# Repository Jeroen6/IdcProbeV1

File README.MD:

# IdcProbeV1
Invasive isolated DC Current probe based on Sensitec CMS3000

## What

This USB 5V powered current sensor should provide an relatively cheap way to safely scope AC or DC current.  
It should provide isolation up to 4 kV (rms), meaning it can measure anywhere in a circuit.

The high bandwidth and accuracy of the Sensitec module made it almost like a normal shunt.

Transfer ratio of the 5A and 15A unit would be 1A:1V and 1A:0.1V respectively.

## Challenges
The challenges involved in this project are powering the Sensitec sensor from a USB port, commonly found on most modern scopes.  
This required a high frequency (1.3 Mhz) DC-DC converter to create positive ands negative 12V for the sensor.  
Several prototypes have shown this is not an easy job, keeping ripple low is difficult with >1 MHz converters.

Due to the capacitance required for the DC-DC converter a high inrush current needs to be reduced on the USB input.

## Progress so far
So far two working prototypes have been made (photo) and used thoroughly this year, it was extremely useful!  
Several important changes to the circuit have been made, both to the DC-DC, the input current, and oscillation prevention on the output with long BNC cables.

*(high-res in media folder)*

However, when (winter)time came to continue this project sad news arrived.  
[Sensitec discontinued the CMS and CDS current sensor families][1], with the [CFS1000][2] chip as alternative.

## Future
The CFS1000 is a more versatile product. Which is an advantage, but not if you required on the engineering and factory calibration of the CMS3000.
The CFS series requires development of an external sensing busbar and calibration procedure, both exceed my initial intended complexity of this project. But I might change my mind.

I will probably not persue development of this project, apart from assembling a few units for peronal use.  

*If someone has ideas to revive this project, let me know (make an issue or something)*

[1]: https://github.com/Jeroen6/IdcProbeV1/blob/master/doc/Sensitec%20-%20CMS3000%20-%20Current%20sensor%20discontinuation%20notice.pdf
[2]: https://github.com/Jeroen6/IdcProbeV1/blob/master/doc/Sensited%20-%20CFS1000%20-%20%20Integrated%20MagnetoResistive%20Current%20Sensor.pdf

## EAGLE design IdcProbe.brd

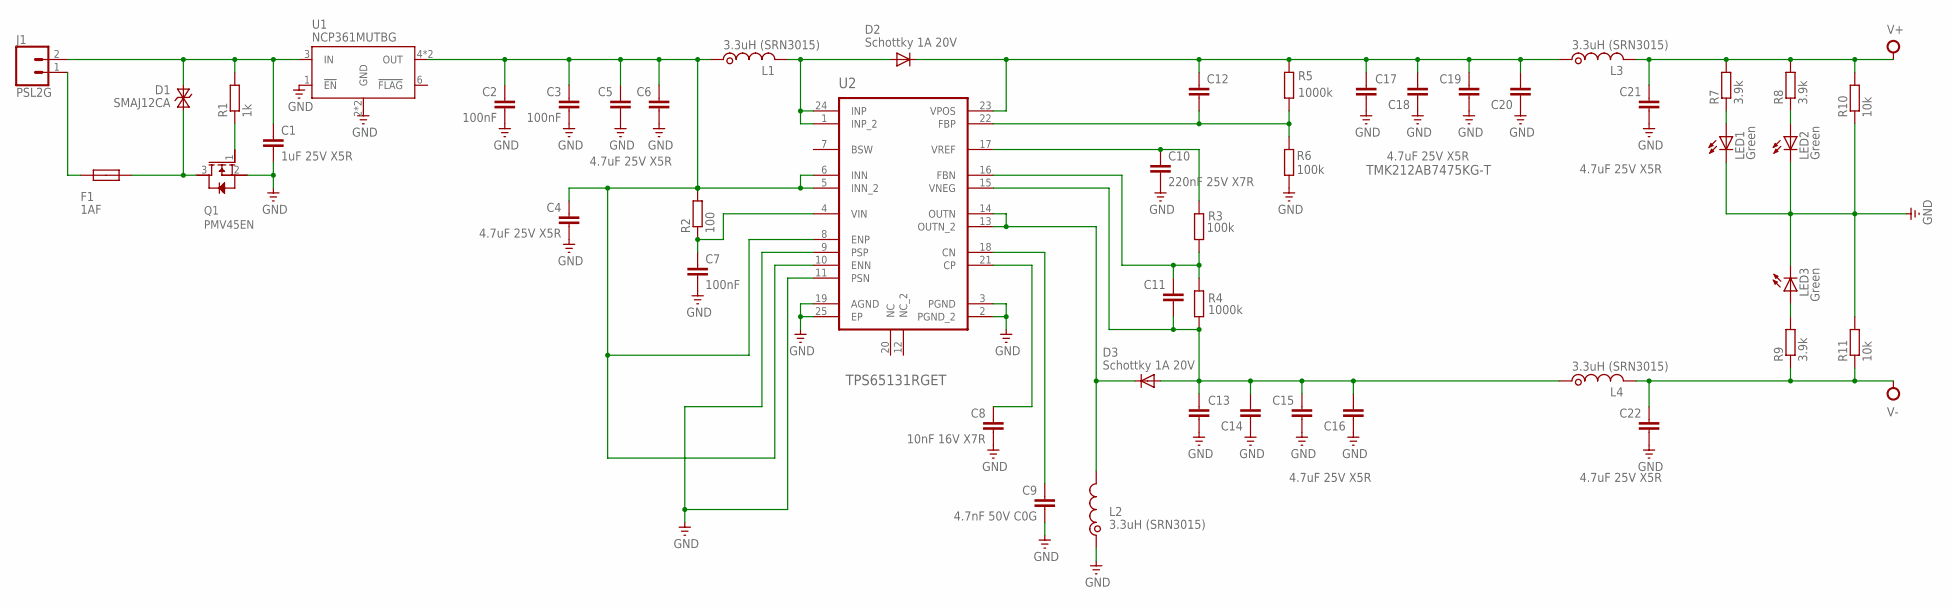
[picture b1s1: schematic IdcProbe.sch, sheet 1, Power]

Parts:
C1: 1uF 25V X5R; C0805; MPN TMK212AB7475KG-T
C2, C3, C7: 100nF; C0805
C4, C5, C6, C13, C14, C15, C16, C17, C18, C19, C20, C21, C22: 4.7uF 25V X5R; C0805; MPN TMK212AB7475KG-T
C8: 10nF 16V X7R; C0805
C9: 4.7nF 50V C0G; C0805
C10: 220nF 25V X7R; C0805
C11, C12: C-EUC0805; C0805
D1: SMAJ12CA; SMA_NOPOL
D2, D3: Schottky 1A 20V; SOD323-R; MPN PMEG4010BEA
F1: 1AF; 1206_HV
J1: PSL2G; MOLEX-1X2
L1, L2, L3, L4: 3.3uH (SRN3015); VLS3015
LED1: Green; LED3MM
LED2, LED3: Green; CHIP-LED0805
Q1: PMV45EN; SOT23
R1: 1k; R0805I
R2: 100; R0805I
R3, R6: 100k; R0805I
R4, R5: 1000k; R0805I
R7, R8, R9: 3.9k; R0805I
R10, R11: 10k; R0805I
U1: NCP361MUTBG; UDFN6_2X2; MPN TMK212AB7475KG-T
U2: TPS65131RGET; QFN50P400X400X100-25N

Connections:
CN: C9.1, U2.18 (CN)
CP: C8.1, U2.21 (CP)
FBN: C11.1, R3.1, R4.1, U2.16 (FBN)
FBP: C12.2, R5.1, R6.2, U2.22 (FBP)
GND: C1.2, C2.2, C3.2, C4.2, C5.2, C6.2, C7.2, C8.2, C9.2, C10.2, C13.2, C14.2, C15.2, C16.2, C17.2, C18.2, C19.2, C20.2, C21.2, C22.2, L2.1, LED1.K (C), LED2.C, LED3.C, Q1.2 (S), R6.1, R10.1, R11.2, U1.1 (!EN), U1.2 (GND), U1.7 (GND), U2.2 (PGND_2), U2.3 (PGND), U2.9 (PSP), U2.11 (PSN), U2.19 (AGND), U2.25 (EP); also elsewhere on the board
INP: D2.A, L1.2, U2.1 (INP_2), U2.24 (INP)
unnamed: LED2.A, R8.1
unnamed: LED3.A, R9.2
unnamed: LED1.A, R7.1
unnamed: C1.1, D1.2 (C), J1.2, R1.2, U1.3 (IN)
unnamed: D1.1 (A), F1.P$1, Q1.3 (D)
unnamed: Q1.1 (G), R1.1
unnamed: F1.P$2, J1.1
OUTN: D3.C, L2.2, U2.13 (OUTN_2), U2.14 (OUTN)
RV+: C12.1, C17.1, C18.1, C19.1, C20.1, D2.C, L3.1, R5.2, U2.23 (VPOS)
RV-: C11.2, C13.1, C14.1, C15.1, C16.1, D3.A, L4.1, R4.2, U2.15 (VNEG)
V+: C21.1, L3.2, R7.2, R8.2, R10.2; also elsewhere on the board
V-: C22.1, L4.2, R9.1, R11.1; also elsewhere on the board
VI: C2.1, C3.1, C4.1, C5.1, C6.1, L1.1, R2.2, U1.4 (OUT), U1.5 (OUT), U2.5 (INN_2), U2.6 (INN), U2.8 (ENP), U2.10 (ENN)
VIN: C7.1, R2.1, U2.4 (VIN)
VREF: C10.1, R3.2, U2.17 (VREF)

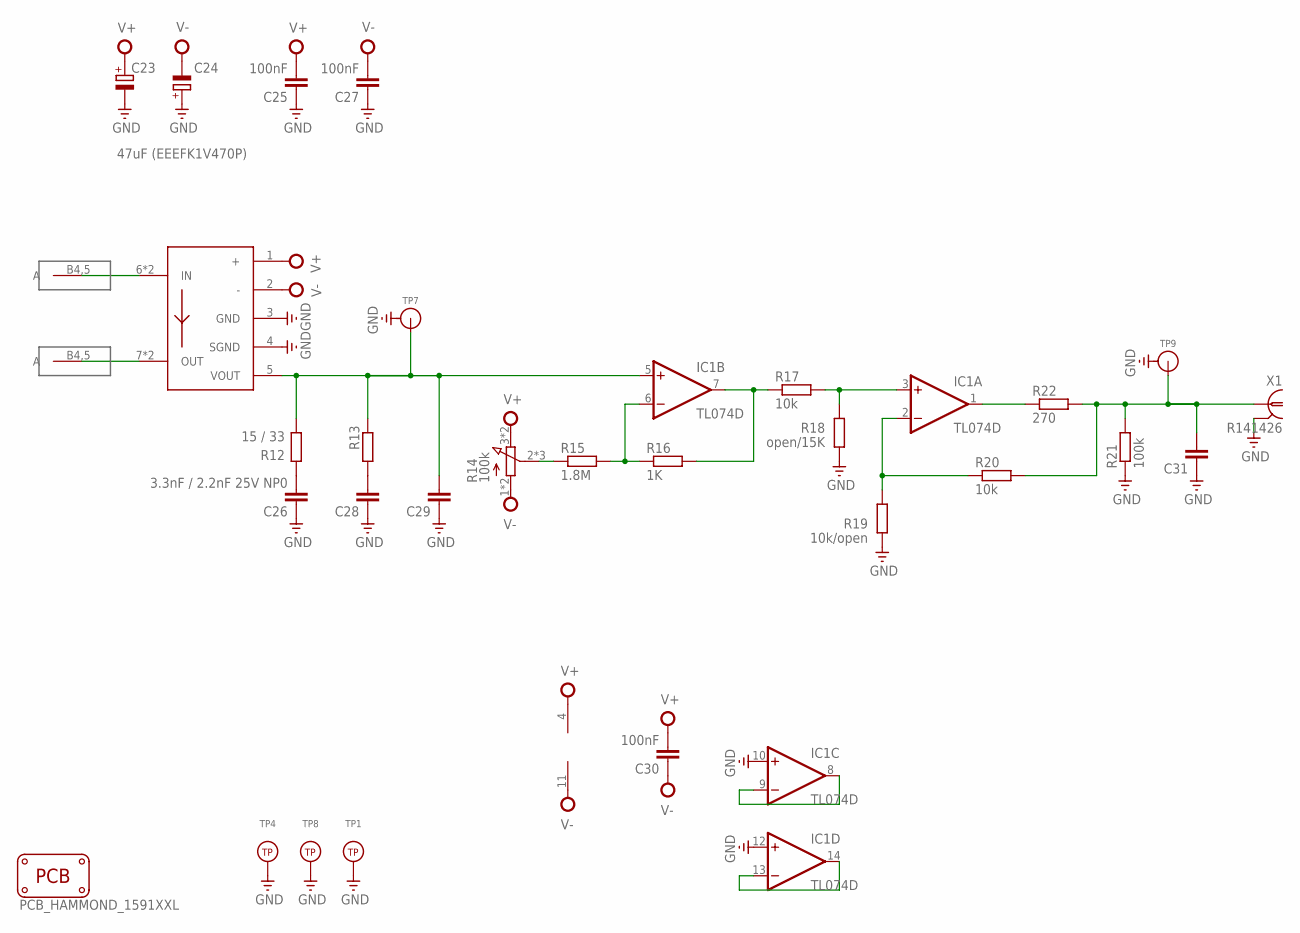
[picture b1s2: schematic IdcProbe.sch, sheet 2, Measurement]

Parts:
C23, C24: 47uF (EEEFK1V470P); PANASONIC_D
C25, C27, C30: 100nF; C0805
C26: 3.3nF / 2.2nF 25V NP0; C0805
C28, C29, C31: C-EUC0805; C0805
H1: PCB_HAMMOND_1591XXL; HMD_MFG_1591XXL
IC1: TL074D; SO14
P1, P2: BANANA_SOCKETVERTICAL; 4,5-PAD
R12: 15 / 33; R0805
R13: R-EU_R0805; R0805
R14: 100k; 3386-MULTI; MPN 3386P-1-104LF
R15: 1.8M; R0805
R16: 1K; R0805
R17, R20: 10k; R0805I
R18: open/15K; R0805I
R19: 10k/open; R0805I
R21: 100k; R0805
R22: 270; R0805
TP1, TP4, TP8: TESTPOINT; TESTHOOK
TP7, TP9: TESTPOINT_GND; PROBE_POINT
U3: CMS3005; CMS3015
X1: R141426

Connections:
GND: C23.-, C24.+, C25.1, C26.1, C27.1, C28.1, C29.1, C31.1, IC1.10 (+IN), IC1.12 (+IN), R18.1, R19.1, R21.1, TP1.TP, TP4.TP, TP7.GND, TP8.TP, TP9.GND, U3.3 (GND), U3.4 (SGND), X1.2, X1.3 (2), X1.4 (2), X1.5 (2); also elsewhere on the board
unnamed: IC1.7 (OUT), R16.2, R17.1
unnamed: IC1.6 (-IN), R15.2, R16.1
unnamed: P1.B4,5, U3.6 (IN), U3.6' (IN)
unnamed: P2.B4,5, U3.7 (OUT), U3.7' (OUT)
unnamed: IC1.8 (OUT), IC1.9 (-IN)
unnamed: IC1.13 (-IN), IC1.14 (OUT)
unnamed: C26.2, R12.2
unnamed: C28.2, R13.2
unnamed: C31.2, R20.2, R21.2, R22.2, TP9.TP, X1.1
unnamed: C29.2, IC1.5 (+IN), R12.1, R13.1, TP7.TP, U3.5 (VOUT)
unnamed: IC1.2 (-IN), R19.2, R20.1
unnamed: R14.2 (SW), R14.5 (SW), R14.7 (SW), R15.1
unnamed: IC1.3 (+IN), R17.2, R18.2
unnamed: IC1.1 (OUT), R22.1
V+: C23.+, C25.2, C30.2, IC1.4 (V+), R14.3 (CW), R14.6 (CW), U3.1 (+); also elsewhere on the board
V-: C24.-, C27.2, C30.1, IC1.11 (V-), R14.1 (CCW), R14.4 (CCW), U3.2 (-); also elsewhere on the board

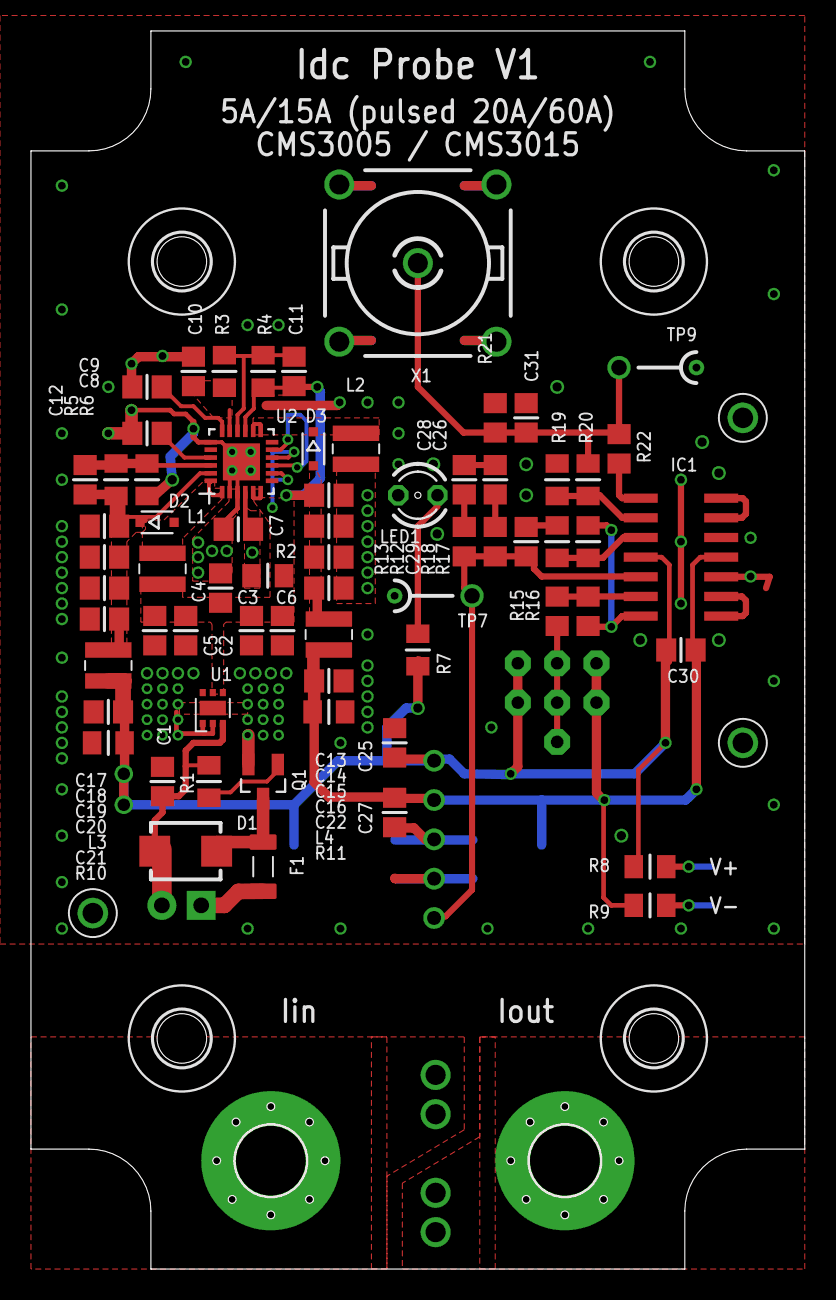
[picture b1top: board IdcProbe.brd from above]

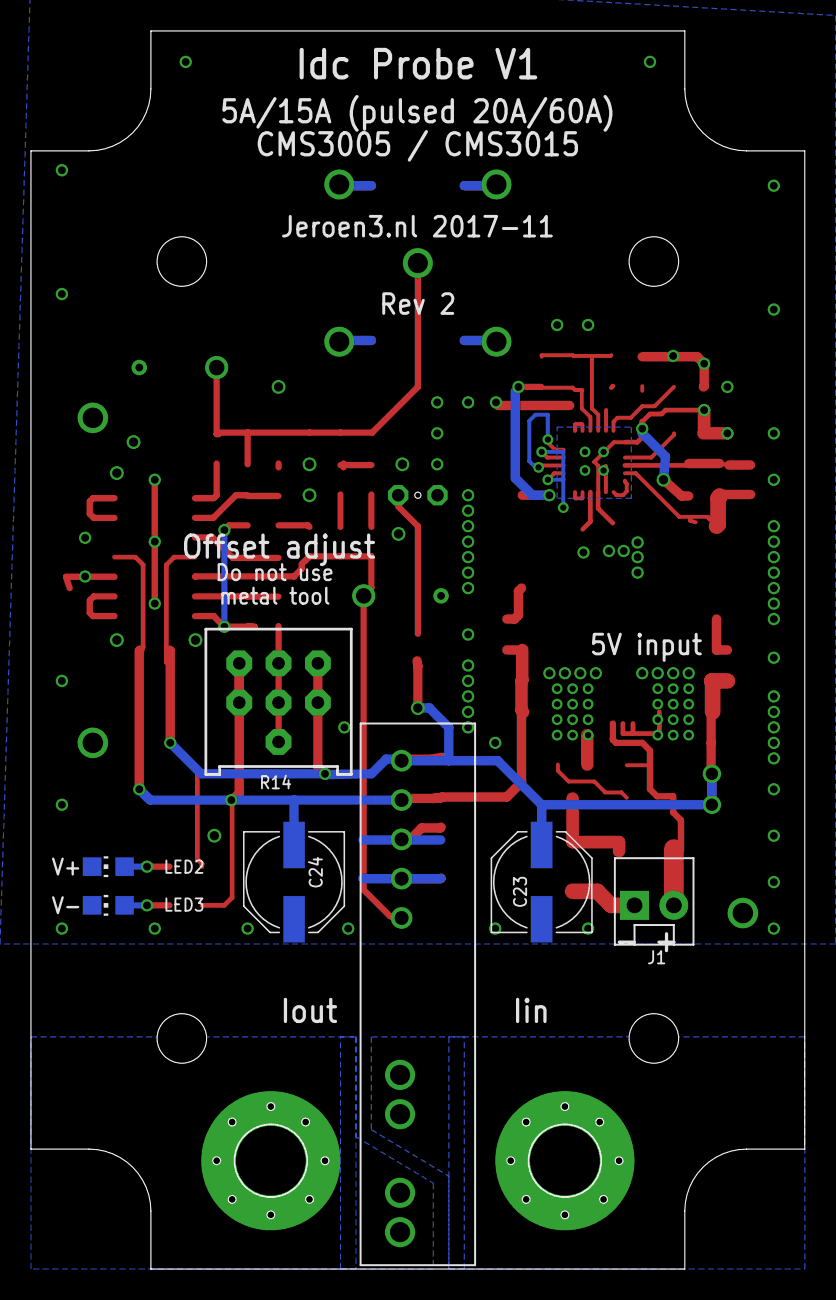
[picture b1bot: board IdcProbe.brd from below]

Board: 2 copper layers, 49.9 x 79.9 mm, 79 parts (7 on the bottom side), 35 nets.

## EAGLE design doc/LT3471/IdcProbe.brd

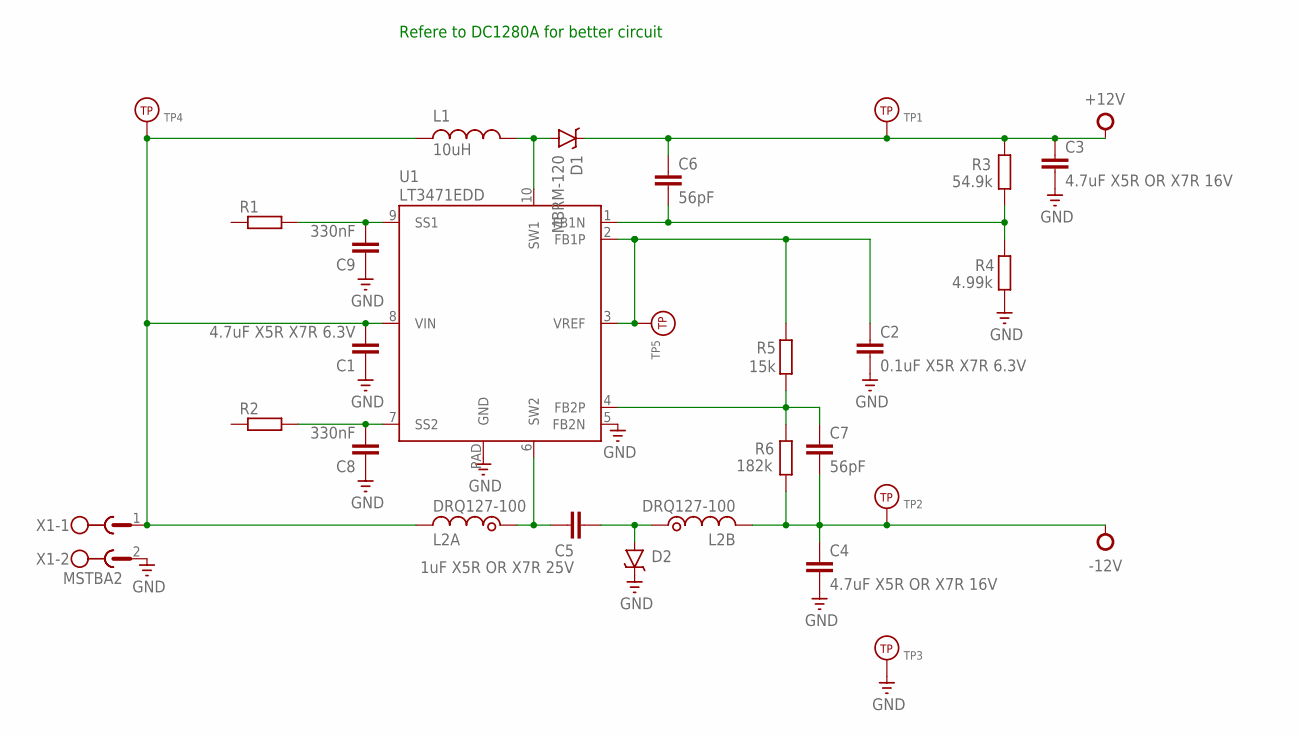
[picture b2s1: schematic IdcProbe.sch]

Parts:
C1: 4.7uF X5R X7R 6.3V; C0603
C2: 0.1uF X5R X7R 6.3V; C0603
C3, C4: 4.7uF X5R OR X7R 16V; C0603
C5: 1uF X5R OR X7R 25V; C0603
C6, C7: 56pF; C0603
C8, C9: 330nF; C0603
D1, D2: MBRM-120; POWERMITE1
L1: 10uH; 242408FPS; MPN 242408FPS‑220M‑01
L2: DRQ127-100; DRQ127
R1, R2: R-EU_R0603; R0603
R3: 54.9k; R0603
R4: 4.99k; R0603
R5: 15k; R0603
R6: 182k; R0603
TP1, TP2, TP3, TP4, TP5: TESTPOINT; TESTHOOK
U1: LT3471EDD; DFN10-3X3
X1: MSTBA2

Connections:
+12V: C3.1, C6.1, D1.1 (C), R3.2, TP1.TP
-12V: C4.1, C7.2, L2.4 (2), R6.1, TP2.TP
GND: C1.1, C2.2, C3.2, C4.2, C8.1, C9.1, D2.1 (C), R4.1, TP3.TP, U1.5 (FB2N), U1.PAD (GND), X1.2
unnamed: C9.2, R1.2, U1.9 (SS1)
unnamed: C8.2, R2.2, U1.7 (SS2)
unnamed: C1.2, L1.1, L2.3 (2), TP4.TP, U1.8 (VIN), X1.1
unnamed: D1.2 (A), L1.2, U1.10 (SW1)
unnamed: C6.2, R3.1, R4.2, U1.1 (FB1N)
unnamed: C7.1, R5.2, R6.2, U1.4 (FB2P)
unnamed: C5.2, L2.1, U1.6 (SW2)
unnamed: C5.1, D2.2 (A), L2.2 (1)
unnamed: C2.1, R5.1, TP5.TP, U1.2 (FB1P), U1.3 (VREF)

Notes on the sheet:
Refere to DC1280A for better circuit

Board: 2 copper layers, 26 parts (0 on the bottom side), 12 nets, no tracks yet.

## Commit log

2017-09-24 initial
2017-10-10 work
2017-10-15 Cleanup
2017-10-16 Ordered
2017-11-08 Update smps
2017-11-12 Update
    - Update SMPS
    - Add supply protection
    - Add documentation
    - Started with attributes for BOM.
    - Added divide gain option
    - Printed pdf and generated gerbers
2017-11-14 Update
    Added fuse.
    Renumbered schematic.
    Created pdf and gerber for review.
2017-11-14 added notes, fixed some values
2017-11-14 Shrunk mounting holes, added LED drill alignment hole
2017-11-21 ordered rev2
2018-11-05 Accumulated fixes during testing for version 1.2
2018-11-05 add media
2018-11-05 Add alternative part CFS1000 datasheet
2018-11-05 add readme
2018-11-05 Readme fixes

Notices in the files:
parts and their libraries:
SparkFun-Connectors: Licensing: Creative Commons ShareAlike 4.0 International - https://creativecommons.org/licenses/by-sa/4.0
